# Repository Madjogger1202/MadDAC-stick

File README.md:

# MadDAC-stick

> USB stick with a **4-channel DAC**: **DAC6574** driven by an **RP2040**, every output buffered by its own **OPA320** op-amp.  
> Plug it into a USB-A port and get four programmable analog voltages.

<p align="center"><i>Board preview (top / bottom) generated from the KiCad board file</i></p>

---

## Overview

MadDAC-stick is the output half of a pair of USB "sticks" (see also [MadADC-stick](https://github.com/Madjogger1202/MadADC-stick)).  
The RP2040 controls a quad I²C DAC; each DAC output goes through a unity-gain **OPA320** buffer to a 4-pin socket, with a second 4-pin row of ground next to it.

---

## What's on the board

| Block | Part | Purpose |
|:--|:--|:--|
| MCU | **RP2040** | USB device, I²C master for the DAC |
| Flash | **W25Q16JV** | 16 Mbit QSPI flash |
| DAC | **DAC6574** | Quad 10-bit voltage-output DAC, I²C |
| Output buffers | 4× **OPA320** | Rail-to-rail voltage followers, one per channel |
| Supply filtering | 4× 10 nH + decoupling | Separate filtered supply for every op-amp |
| Power | **RT6150B-33** buck-boost | 5 V USB → 3.3 V |
| Clock | ABM8-272-T3 crystal | RP2040 reference clock |
| USB | USB-A plug | Power and data, plugs directly into a host port |
| Button | KMR221 | Boot button |

---

## Pinout

**RP2040 ↔ DAC6574**

| RP2040 GPIO | Signal | Notes |
|:--|:--|:--|
| GPIO4 | `SDA` | I²C data, 4.7 kΩ pull-up |
| GPIO5 | `SCL` | I²C clock, 4.7 kΩ pull-up |

DAC address pins `A0` and `A1` are tied to GND.

**Analog socket (2× 4-pin, 2.54 mm)**

| Pin | Row J2 | Row J3 |
|:--|:--|:--|
| 1 | `OUT A` (buffered) | GND |
| 2 | `OUT B` (buffered) | GND |
| 3 | `OUT C` (buffered) | GND |
| 4 | `OUT D` (buffered) | GND |

---

## Specifications

| Parameter | Value |
|:--|:--|
| Board outline | 39.0 × 16.8 mm |
| Layers | 2 |
| Thickness | 1.6 mm |
| Supply | 5 V from a USB-A port |
| Components | 53 |
| Revision | rev0 |

---

## Repository structure

```
MadDAC-stick.kicad_sch   — schematic
MadDAC-stick.kicad_pcb   — PCB layout
MadDAC-stick-backups/    — KiCad automatic backups
img/                     — board previews
```

---

## Development environment

- **Schematic & PCB:** KiCad 9
- **Firmware:** Pico SDK / Arduino-Pico / PlatformIO (RP2040) — not included in this repository

---

*by [@madjogger](https://t.me/madjogger)*

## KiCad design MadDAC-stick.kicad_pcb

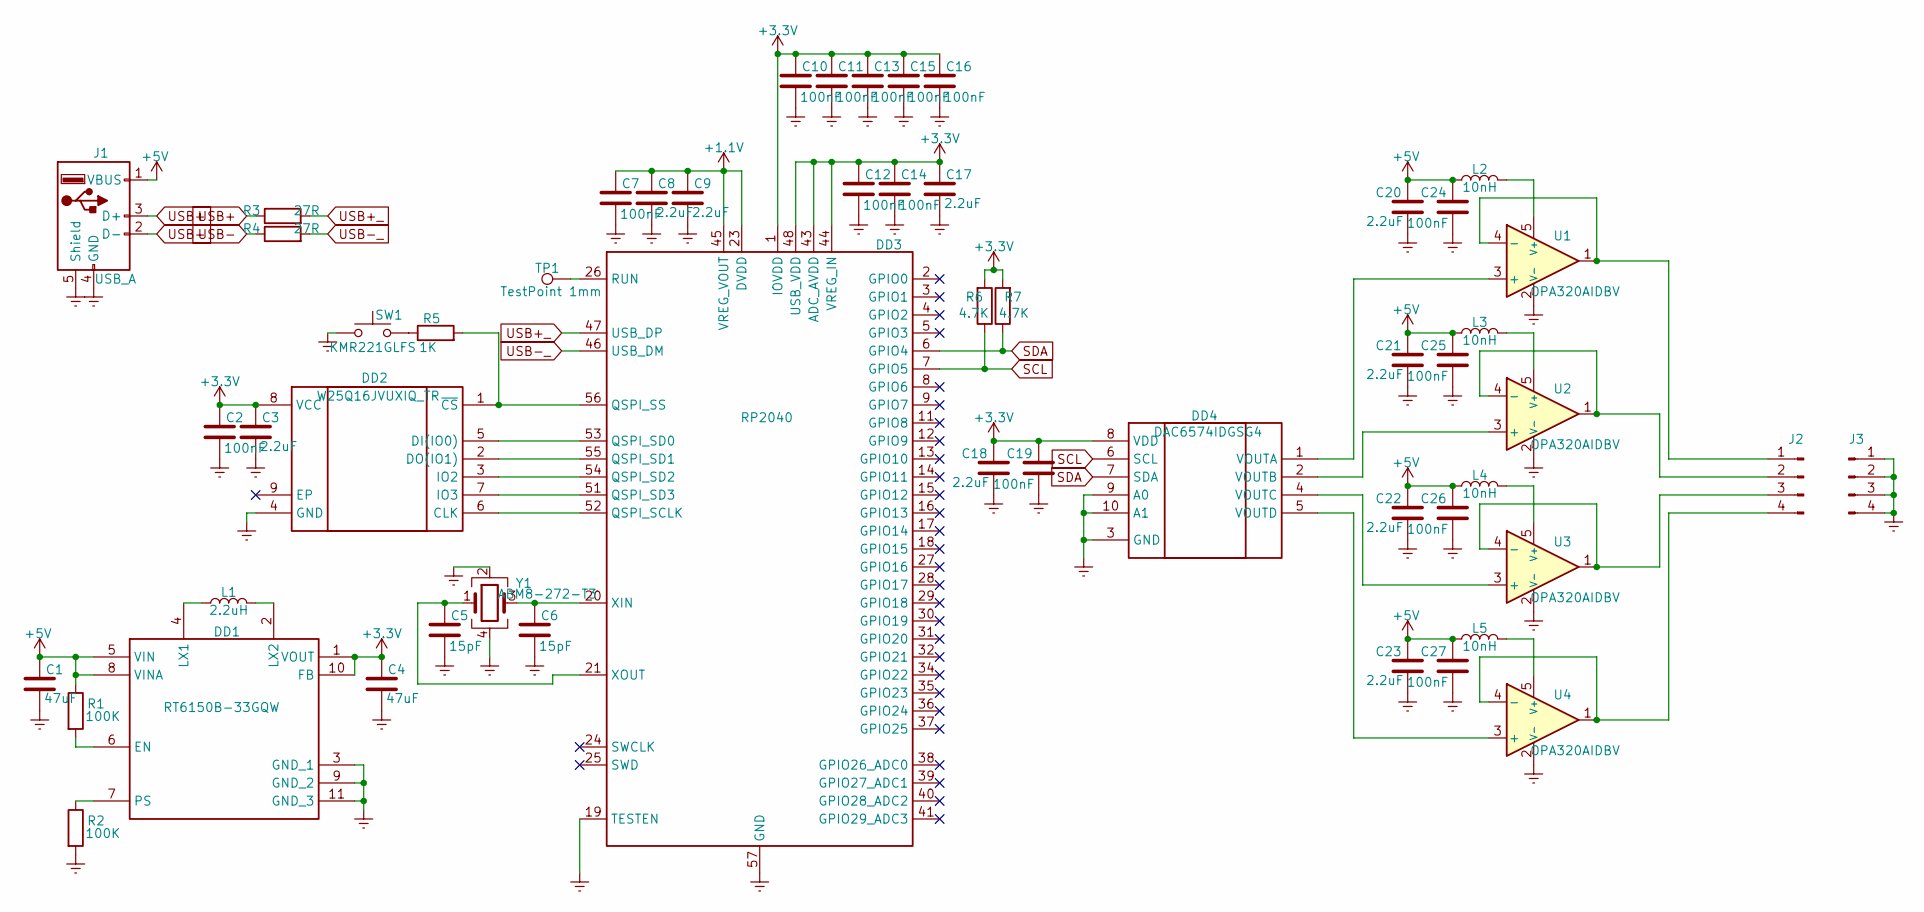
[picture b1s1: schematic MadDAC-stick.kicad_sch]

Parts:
C1, C4: 47uF; C_0805_2012Metric
C2, C7, C10, C11, C12, C13, C14, C15, C16, C19, C24, C25, C26, C27: 100nF; C_0201_0603Metric
C3, C8, C9, C17, C18, C20, C21, C22, C23: 2.2uF; C_0402_1005Metric
C5, C6: 15pF; C_0201_0603Metric
DD1: RT6150B-33GQW; Manufacturer_Part_Number RT6150B-33GQW; Mouser Part Number 835-RT6150B-33GQW
DD2: W25Q16JVUXIQ_TR; W25Q16JVUXIQ; Manufacturer_Part_Number W25Q16JVUXIQ TR; Mouser Part Number 454-W25Q16JVUXIQTR
DD3: RP2040; QFN-56-1EP_7x7mm_P0.4mm_EP3.2x3.2mm
DD4: DAC6574IDGSG4; DAC6574IDGS; Manufacturer_Part_Number DAC6574IDGSG4; Mouser Part Number 595-DAC6574IDGSG4
J1: USB_A; USB_A_Connfly_DS1098_Horizontal
J2, J3: Conn_01x04_Pin; PinSocket_1x04_P2.54mm_Vertical
L1: 2.2uH; L_1008_2520Metric
L2, L3, L4, L5: 10nH; L_0603_1608Metric
R1, R2: 100K; R_0402_1005Metric
R3, R4: 27R; R_0201_0603Metric
R5: 1K; R_0402_1005Metric
R6, R7: 4.7K; R_0402_1005Metric
SW1: KMR221GLFS; SW_SPST_PTS810
TP1: TestPoint 1mm; TestPoint_Pad_D1.0mm
U1, U2, U3, U4: OPA320AIDBV; SOT-23-5
Y1: ABM8-272-T3; Crystal_SMD_3225-4Pin_3.2x2.5mm

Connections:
+1.1V: C7.1, C8.1, C9.1, DD3.23 (DVDD), DD3.45 (VREG_VOUT), DD3.50 (DVDD)
+3.3V: C2.1, C3.1, C4.1, C10.1, C11.1, C12.1, C13.1, C14.1, C15.1, C16.1, C17.1, C18.1, C19.1, DD1.1 (VOUT), DD1.10 (FB), DD2.8 (VCC), DD3.1 (IOVDD), DD3.10 (IOVDD), DD3.22 (IOVDD), DD3.33 (IOVDD), DD3.42 (IOVDD), DD3.43 (ADC_AVDD), DD3.44 (VREG_IN), DD3.48 (USB_VDD), DD3.49 (IOVDD), DD4.8 (VDD), R6.2, R7.2
+5V: C1.1, C20.1, C21.1, C22.1, C23.1, C24.1, C25.1, C26.1, C27.1, DD1.5 (VIN), DD1.8 (VINA), J1.1 (VBUS), L2.1, L3.1, L4.1, L5.1, R1.1
Earth: C1.2, C2.2, C3.2, C4.2, C5.2, C6.2, C7.2, C8.2, C9.2, C10.2, C11.2, C12.2, C13.2, C14.2, C15.2, C16.2, C17.2, C18.2, C19.2, C20.2, C21.2, C22.2, C23.2, C24.2, C25.2, C26.2, C27.2, DD1.3 (GND_1), DD1.9 (GND_2), DD1.11 (GND_3), DD2.4 (GND), DD3.19 (TESTEN), DD3.57 (GND), DD4.3 (GND), DD4.9 (A0), DD4.10 (A1), J1.4 (GND), J1.5 (Shield), J3.1, J3.2, J3.3, J3.4, R2.2, SW1.1, U1.2 (V-), U2.2 (V-), U3.2 (V-), U4.2 (V-), Y1.2, Y1.4
unnamed: DD1.6 (EN), R1.2
unnamed: DD1.4 (LX1), L1.1
unnamed: DD1.2 (LX2), L1.2
unnamed: DD1.7 (PS), R2.1
unnamed: DD2.6 (CLK), DD3.52 (QSPI_SCLK)
unnamed: DD2.5 (DI(IO0)), DD3.53 (QSPI_SD0)
unnamed: DD2.2 (DO(IO1)), DD3.55 (QSPI_SD1)
unnamed: DD2.3 (IO2), DD3.54 (QSPI_SD2)
unnamed: DD2.7 (IO3), DD3.51 (QSPI_SD3)
unnamed: DD2.1 (~CS), DD3.56 (QSPI_SS), R5.2
unnamed: DD3.26 (RUN), TP1.1
unnamed: C6.1, DD3.20 (XIN), Y1.3
unnamed: C5.1, DD3.21 (XOUT), Y1.1
unnamed: DD4.1 (VOUTA), U1.3 (+)
unnamed: DD4.2 (VOUTB), U2.3 (+)
unnamed: DD4.4 (VOUTC), U3.3 (+)
unnamed: DD4.5 (VOUTD), U4.3 (+)
unnamed: J2.1, U1.1, U1.4 (-)
unnamed: J2.2, U2.1, U2.4 (-)
unnamed: J2.3, U3.1, U3.4 (-)
unnamed: J2.4, U4.1, U4.4 (-)
unnamed: R5.1, SW1.2
unnamed: L2.2, U1.5 (V+)
unnamed: L3.2, U2.5 (V+)
unnamed: L4.2, U3.5 (V+)
unnamed: L5.2, U4.5 (V+)
SCL: DD3.7 (GPIO5), DD4.6 (SCL), R6.1
SDA: DD3.6 (GPIO4), DD4.7 (SDA), R7.1
USB+: J1.3 (D+), R3.1
USB+_: DD3.47 (USB_DP), R3.2
USB-: J1.2 (D-), R4.1
USB-_: DD3.46 (USB_DM), R4.2

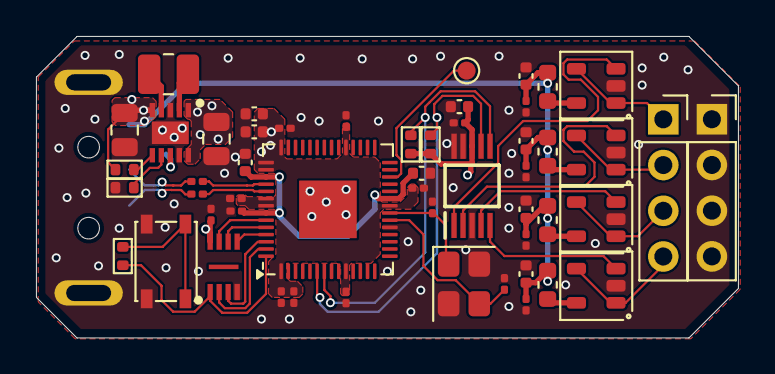
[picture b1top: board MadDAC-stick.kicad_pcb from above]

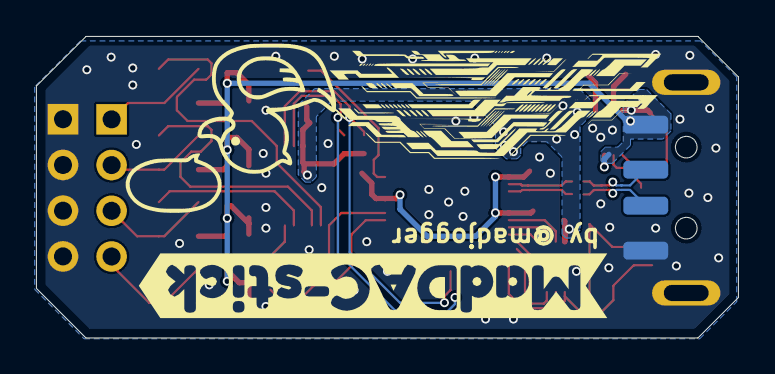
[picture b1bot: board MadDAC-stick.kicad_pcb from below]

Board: 2 copper layers, 39.0 x 16.8 mm, 54 parts (2 on the bottom side), 36 nets.

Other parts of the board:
kibuzzard-69546F3B: G***; kibuzzard-69546F3B

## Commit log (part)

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2025-12-31 rev0 ready
